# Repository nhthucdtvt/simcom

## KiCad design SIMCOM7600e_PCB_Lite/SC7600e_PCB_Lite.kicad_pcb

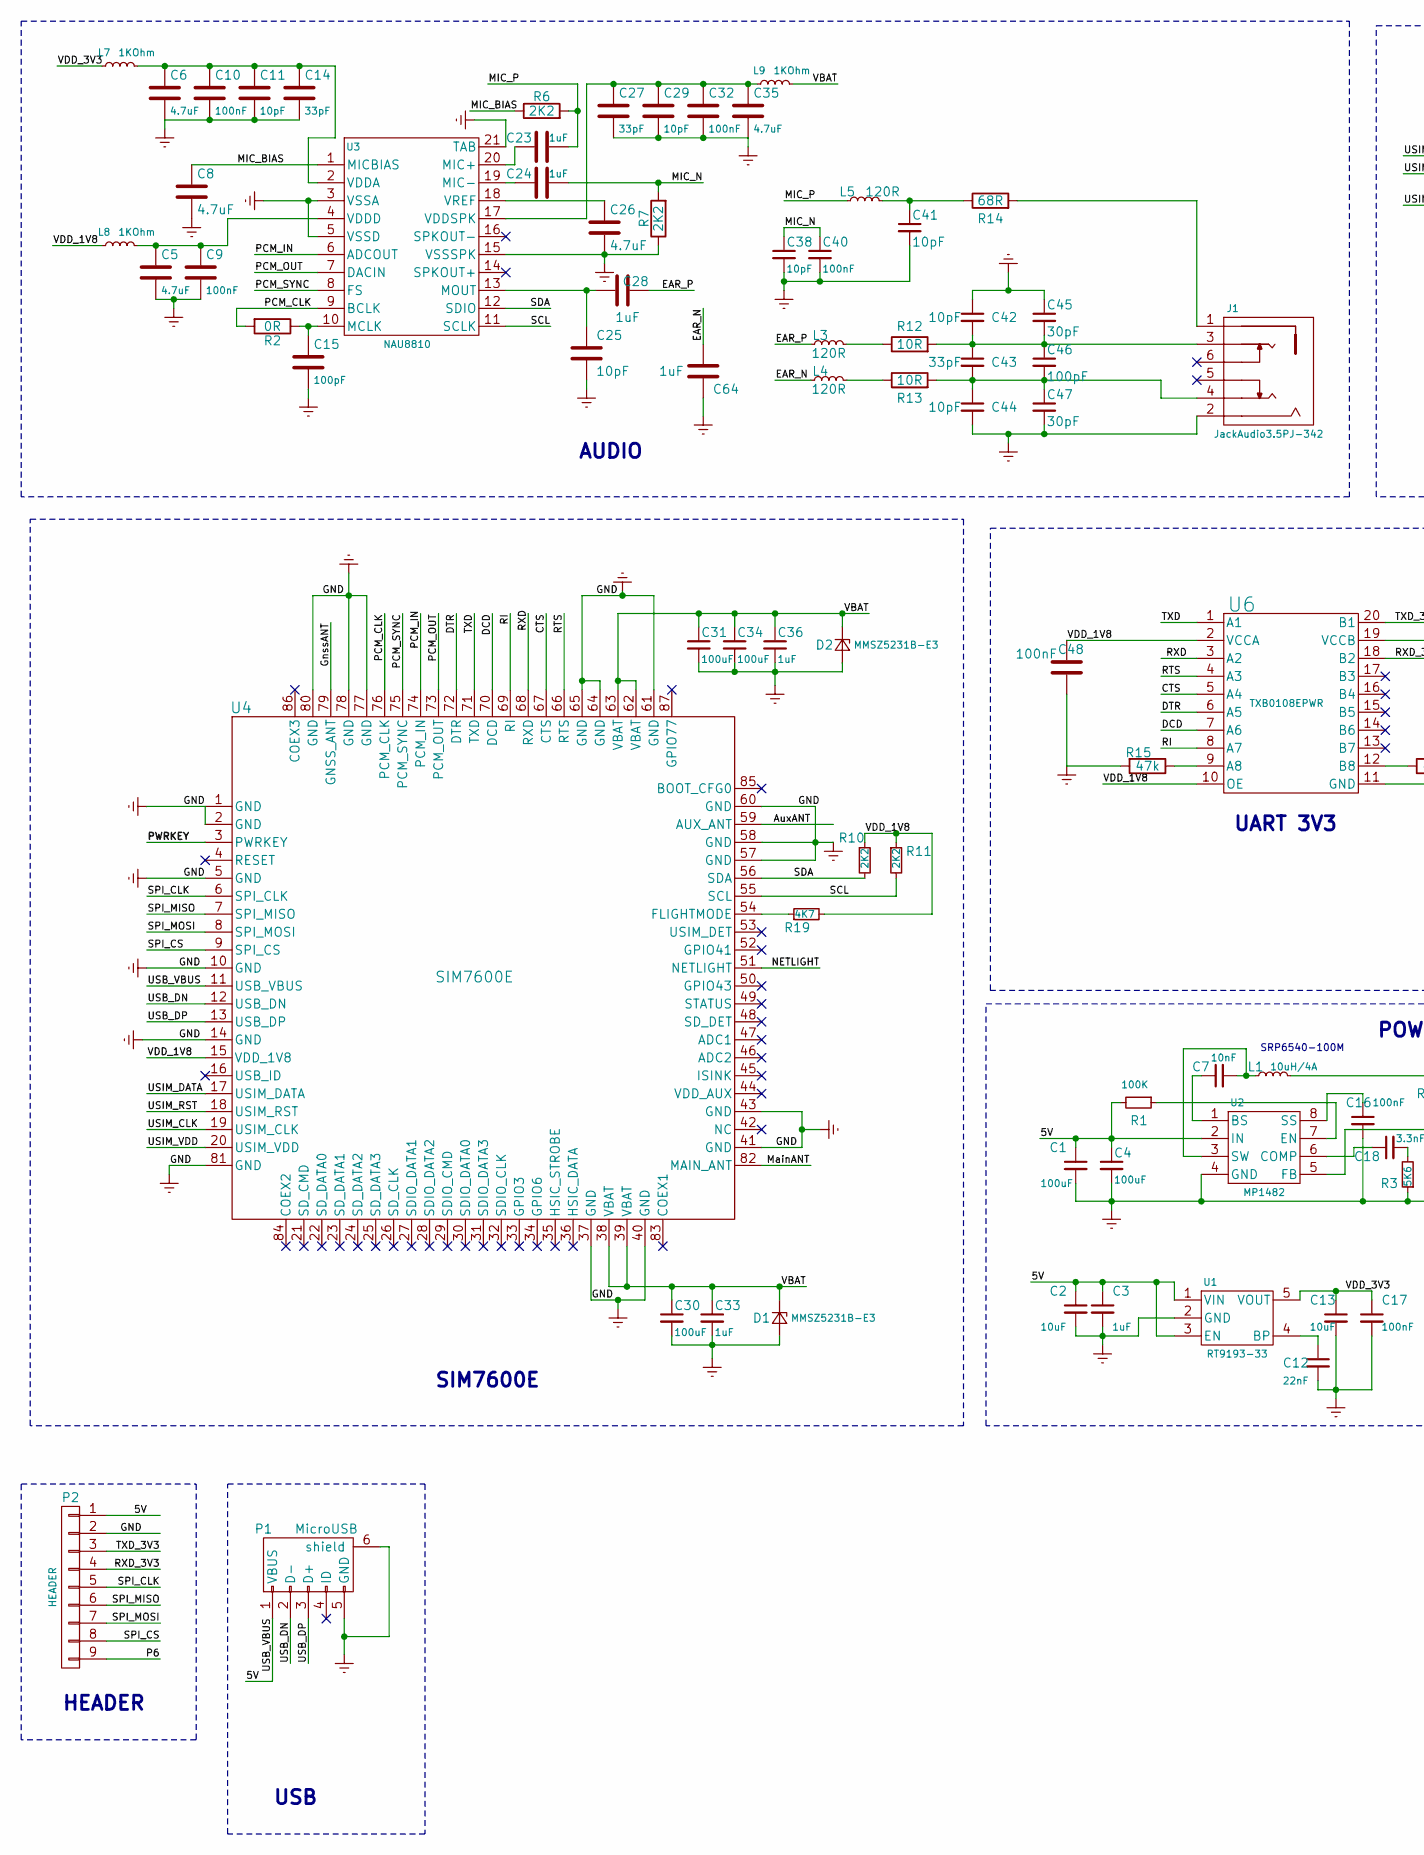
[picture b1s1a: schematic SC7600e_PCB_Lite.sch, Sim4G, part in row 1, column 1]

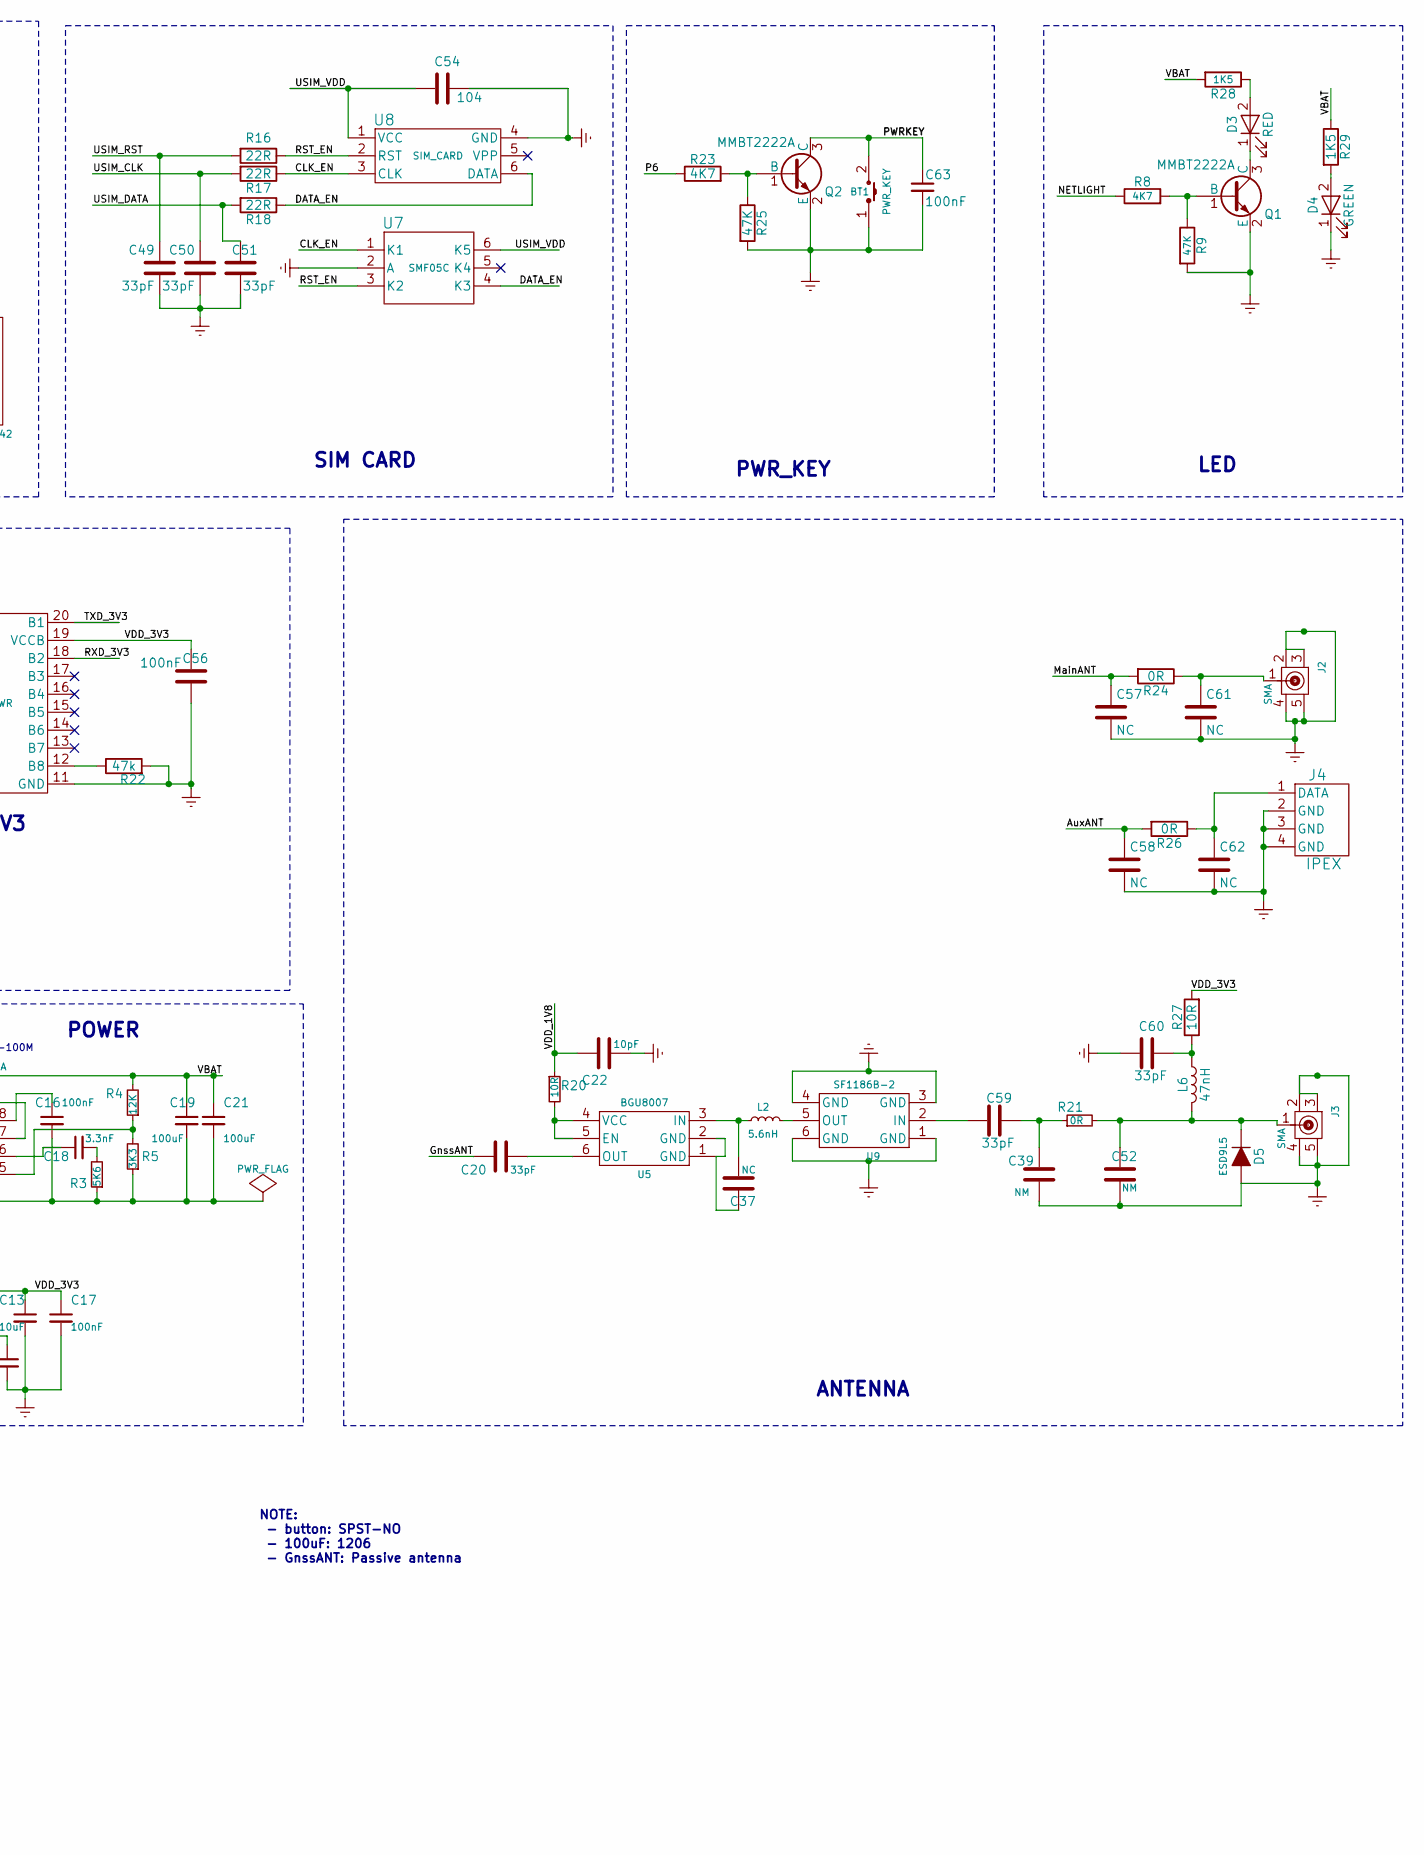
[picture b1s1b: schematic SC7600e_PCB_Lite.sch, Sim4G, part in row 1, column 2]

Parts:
BT1: PWR_KEY; SW_SPST_REED_CT05-XXXX-G1
C1, C19, C21, C30, C31, C34: 100uF; C_0805_2012Metric
C2, C13: 10uF; C_0603_1608Metric
C3, C23, C24, C28, C33, C36, C64: 1uF; C_0603_1608Metric
C4: 100uF; C_0603_1608Metric
C5, C6, C8, C26, C35: 4.7uF; C_0603_1608Metric
C7: 10nF; C_0603_1608Metric
C9, C10, C16, C17, C32, C40, C48, C56, C63: 100nF; C_0603_1608Metric
C11, C22, C25, C29, C38, C41, C42, C44: 10pF; C_0603_1608Metric
C12: 22nF; C_0603_1608Metric
C14, C27, C43, C49, C50, C51: 33pF; C_0603_1608Metric
C15, C46: 100pF; C_0603_1608Metric
C18: 3.3nF; C_0603_1608Metric
C20, C59, C60: 33pF; C_0402_1005Metric
C37, C57, C58, C61, C62: NC; C_0402_1005Metric
C39, C52: NM; C_0402_1005Metric
C45, C47: 30pF; C_0603_1608Metric
C54: 104; C_0603_1608Metric
D1, D2: MMSZ5231B-E3; D_SOD-123
D3: RED; LED_0603_1608Metric
D4: GREEN; LED_0603_1608Metric
D5: ESD9L5; SOD-923
J1: JackAudio3.5PJ-342; JackAudio3.5MM-PJ-342-6P
J2, J3: SMA; SMA_6x6x5.3_Vertical
J4: IPEX; IPEX_M_2.6x2.6x2
L1: 10uH/4A; L_7.2x6.5
L2: 5.6nH; L_0402_1005Metric
L3, L4, L5: 120R; R_0603_1608Metric
L6: 47nH; R_0402_1005Metric
L7: 1KOhm; R_0603_1608Metric
L8, L9: 1KOhm; L_0603_1608Metric
P1: MicroUSB; USB_Micro-B_Molex_47346-0001
P2: HEADER; Molex_KK-254_AE-6410-09A_1x09_P2.54mm_Vertical
Q1, Q2: MMBT2222A; SOT-23
R1: 100K; R_0603_1608Metric
R2: 0R; R_0603_1608Metric
R3: 5K6; R_0603_1608Metric
R4: 12K; R_0603_1608Metric
R5: 3K3; R_0603_1608Metric
R6, R7, R10, R11: 2K2; R_0603_1608Metric
R8, R19, R23: 4K7; R_0603_1608Metric
R9, R25: 47K; R_0603_1608Metric
R12, R13, R20, R27: 10R; R_0603_1608Metric
R14: 68R; R_0603_1608Metric
R15, R22: 47k; R_0603_1608Metric
R16, R17, R18: 22R; R_0603_1608Metric
R21, R24, R26: 0R; R_0402_1005Metric
R28, R29: 1K5; R_0603_1608Metric
U1: RT9193-33; SOT-23-5
U2: MP1482; SOIC-8_3.9x4.9mm_P1.27mm
U3: NAU8810; QFN-20-1EP_4x4mm_P0.5mm_EP2.5x2.5mm_ThermalVias
U4: SIM7600E
U5: BGU8007; SOT-886
U6: TXB0108EPWR; TSSOP-20_4.4x6.5mm_P0.65mm
U7: SMF05C; SC70-6
U8: SIM_CARD; CONN-GCT-SIM8050
U9: SF1186B-2; SF1186B2

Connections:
/5V: C1.1, C2.1, C3.1, C4.1, P1.1 (VBUS), P2.1, R1.2, U1.1 (VIN), U1.3 (EN), U2.2 (IN), U4.11 (USB_VBUS)
/AuxANT: C58.1, R26.2, U4.59 (AUX_ANT)
/CLK_EN: R17.1, U7.1 (K1), U8.3 (CLK)
/CTS: U4.67 (CTS), U6.5 (A4)
/DATA_EN: R18.1, U7.4 (K3), U8.6 (DATA)
/DCD: U4.70 (DCD), U6.7 (A6)
/DTR: U4.72 (DTR), U6.6 (A5)
/EAR_N: C64.1, L4.1
/EAR_P: C28.2, L3.1
/GnssANT: C20.1, U4.79 (GNSS_ANT)
/MIC_BIAS: C8.1, R6.1, U3.1 (MICBIAS)
/MIC_N: C24.2, C38.1, C40.1, R7.2
/MIC_P: C23.2, L5.1, R6.2
/MainANT: C57.1, R24.2, U4.82 (MAIN_ANT)
/NETLIGHT: R8.1, U4.51 (NETLIGHT)
/P6: P2.9, R23.1
/PCM_CLK: R2.2, U3.9 (BCLK), U4.76 (PCM_CLK)
/PCM_IN: U3.6 (ADCOUT), U4.74 (PCM_IN)
/PCM_OUT: U3.7 (DACIN), U4.73 (PCM_OUT)
/PCM_SYNC: U3.8 (FS), U4.75 (PCM_SYNC)
/PWRKEY: BT1.2, C63.1, Q2.3 (C), U4.3 (PWRKEY)
/RI: U4.69 (RI), U6.8 (A7)
/RST_EN: R16.1, U7.3 (K2), U8.2 (RST)
/RTS: U4.66 (RTS), U6.4 (A3)
/RXD: U4.68 (RXD), U6.3 (A2)
/RXD_3V3: P2.4, U6.18 (B2)
/SCL: R11.2, U3.11 (SCLK), U4.55 (SCL)
/SDA: R10.2, U3.12 (SDIO), U4.56 (SDA)
/SPI_CLK: P2.5, U4.6 (SPI_CLK)
/SPI_CS: P2.8, U4.9 (SPI_CS)
/SPI_MISO: P2.6, U4.7 (SPI_MISO)
/SPI_MOSI: P2.7, U4.8 (SPI_MOSI)
/TXD: U4.71 (TXD), U6.1 (A1)
/TXD_3V3: P2.3, U6.20 (B1)
/USB_DN: P1.2 (D-), U4.12 (USB_DN)
/USB_DP: P1.3 (D+), U4.13 (USB_DP)
/USIM_CLK: C50.2, R17.2, U4.19 (USIM_CLK)
/USIM_DATA: C51.2, R18.2, U4.17 (USIM_DATA)
/USIM_RST: C49.2, R16.2, U4.18 (USIM_RST)
/USIM_VDD: C54.2, U4.20 (USIM_VDD), U7.6 (K5), U8.1 (VCC)
/VBAT: C19.1, C21.1, C30.1, C31.1, C33.1, C34.1, C36.1, D1.1 (K), D2.1 (K), L1.2, L9.2, R4.2, R28.2, R29.1, U4.38 (VBAT), U4.39 (VBAT), U4.62 (VBAT), U4.63 (VBAT)
/VDD_1V8: C22.1, C48.2, L8.1, R10.1, R11.1, R19.2, R20.1, U4.15 (VDD_1V8), U6.2 (VCCA), U6.10 (OE)
/VDD_3V3: C13.1, C17.1, C56.2, L7.1, R27.2, U1.5 (VOUT), U6.19 (VCCB)
Earth: BT1.1, C1.2, C2.2, C3.2, C4.2, C5.2, C6.2, C8.2, C9.2, C10.2, C11.2, C12.2, C13.2, C14.2, C15.2, C16.2, C17.2, C19.2, C21.2, C22.2, C25.2, C26.2, C27.2, C29.2, C30.2, C31.2, C32.2, C33.2, C34.2, C35.2, C36.2, C38.2, C39.1, C40.2, C41.2, C42.1, C44.2, C45.1, C47.2, C48.1, C49.1, C50.1, C51.1, C52.1, C54.1, C56.1, C57.2, C58.2, C60.2, C61.2, C62.2, C63.2, C64.2, D1.2 (A), D2.2 (A), D4.1 (K), D5.2 (A), J1.2, J2.2, J2.3, J2.4, J2.5, J3.2, J3.3, J3.4, J3.5, J4.2 (GND), J4.3 (GND), J4.4 (GND), P1.5 (GND), P1.6 (shield), P2.2, Q1.2 (E), Q2.2 (E), R3.1, R5.1, R7.1, R9.2, R15.2, R22.2, R25.2, U1.2 (GND), U2.4 (GND), U3.3 (VSSA), U3.5 (VSSD), U3.15 (VSSSPK), U3.21 (TAB), U4.1 (GND), U4.2 (GND), U4.5 (GND), U4.10 (GND), U4.14 (GND), U4.37 (GND), U4.40 (GND), U4.41 (GND), U4.43 (GND), U4.57 (GND), U4.58 (GND), U4.60 (GND), U4.61 (GND), U4.64 (GND), U4.65 (GND), U4.77 (GND), U4.78 (GND), U4.80 (GND), U4.81 (GND), U6.11 (GND), U7.2 (A), U8.4 (GND), U9.1 (GND), U9.3 (GND), U9.4 (GND), U9.6 (GND)
unnamed: C5.1, C9.1, L8.2, U3.4 (VDDD)
unnamed: C7.1, U2.1 (BS)
unnamed: C7.2, L1.1, U2.3 (SW)
unnamed: C6.1, C10.1, C11.1, C14.1, L7.2, U3.2 (VDDA)
unnamed: C12.1, U1.4 (BP)
unnamed: C15.1, R2.1, U3.10 (MCLK)
unnamed: C16.1, U2.8 (SS)
unnamed: C18.1, U2.6 (COMP)
unnamed: C18.2, R3.2
unnamed: C20.2, U5.6 (OUT)
unnamed: C23.1, U3.20 (MIC+)
unnamed: C24.1, U3.19 (MIC-)
unnamed: C25.1, C28.1, U3.13 (MOUT)
unnamed: C26.1, U3.18 (VREF)
unnamed: C27.1, C29.1, C32.1, C35.1, L9.1, U3.17 (VDDSPK)
unnamed: C37.1, U5.1 (GND), U5.2 (GND)
unnamed: C37.2, L2.1, U5.3 (IN)
unnamed: C39.2, C59.1, R21.1
unnamed: C41.1, L5.2, R14.1
unnamed: C42.2, C43.1, C45.2, C46.1, J1.3, R12.2
unnamed: C43.2, C44.1, C46.2, C47.1, J1.4, R13.2
unnamed: C52.2, D5.1 (K), J3.1, L6.2, R21.2
unnamed: C59.2, U9.2 (IN)
unnamed: C60.1, L6.1, R27.1
unnamed: C61.1, J2.1, R24.1
unnamed: C62.1, J4.1 (DATA), R26.1
unnamed: D3.1 (K), Q1.3 (C)
unnamed: D3.2 (A), R28.1
unnamed: D4.2 (A), R29.2
unnamed: J1.1, R14.2
unnamed: L2.2, U9.5 (OUT)
unnamed: L3.2, R12.1
unnamed: L4.2, R13.1
unnamed: Q1.1 (B), R8.2, R9.1
unnamed: Q2.1 (B), R23.2, R25.1
unnamed: R1.1, U2.7 (EN)
unnamed: R4.1, R5.2, U2.5 (FB)
unnamed: R15.1, U6.9 (A8)
unnamed: R19.1, U4.54 (FLIGHTMODE)
unnamed: R20.2, U5.4 (VCC), U5.5 (EN)
unnamed: R22.1, U6.12 (B8)

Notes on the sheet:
ANTENNA
PWR_KEY
LED
SIM CARD
UART 3V3
USB
AUDIO
SIM7600E
POWER
HEADER
NOTE: - button: SPST-NO - 100uF: 1206 - GnssANT: Passive antenna
SRP6540-100M

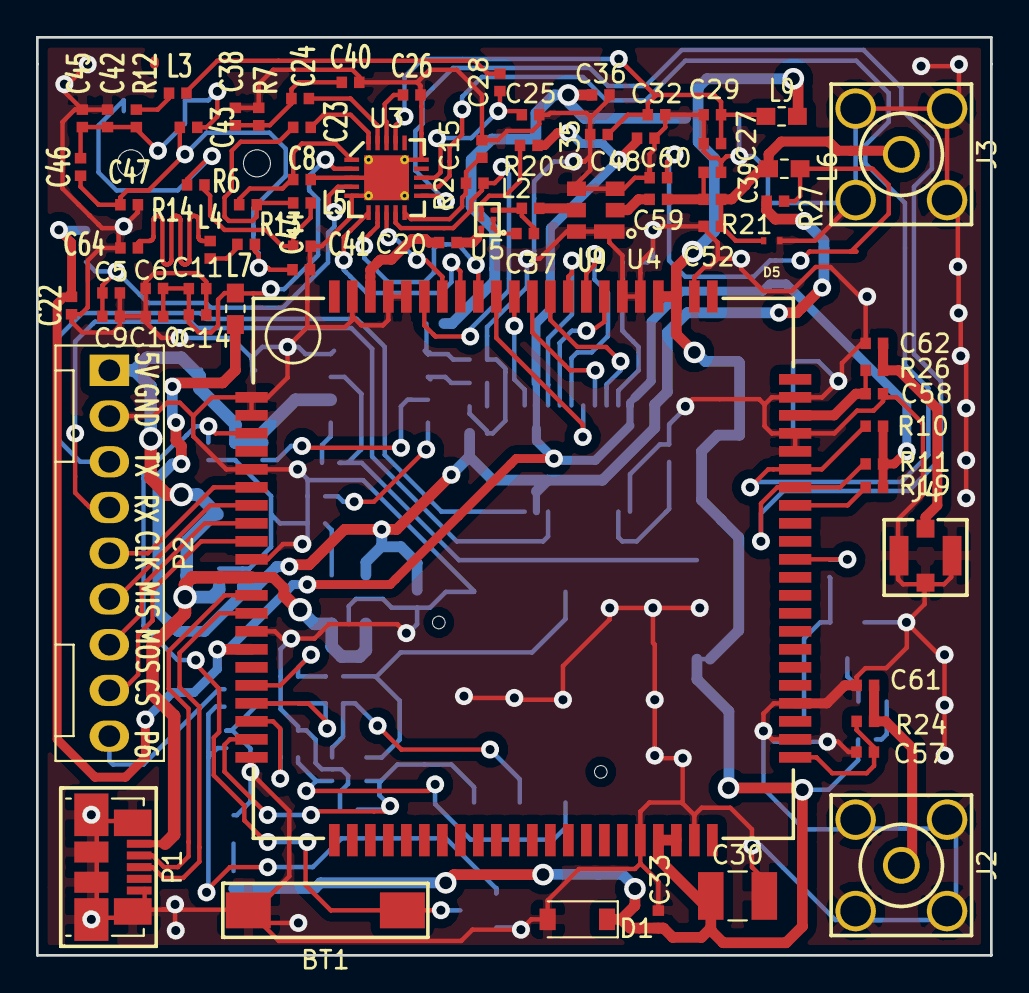
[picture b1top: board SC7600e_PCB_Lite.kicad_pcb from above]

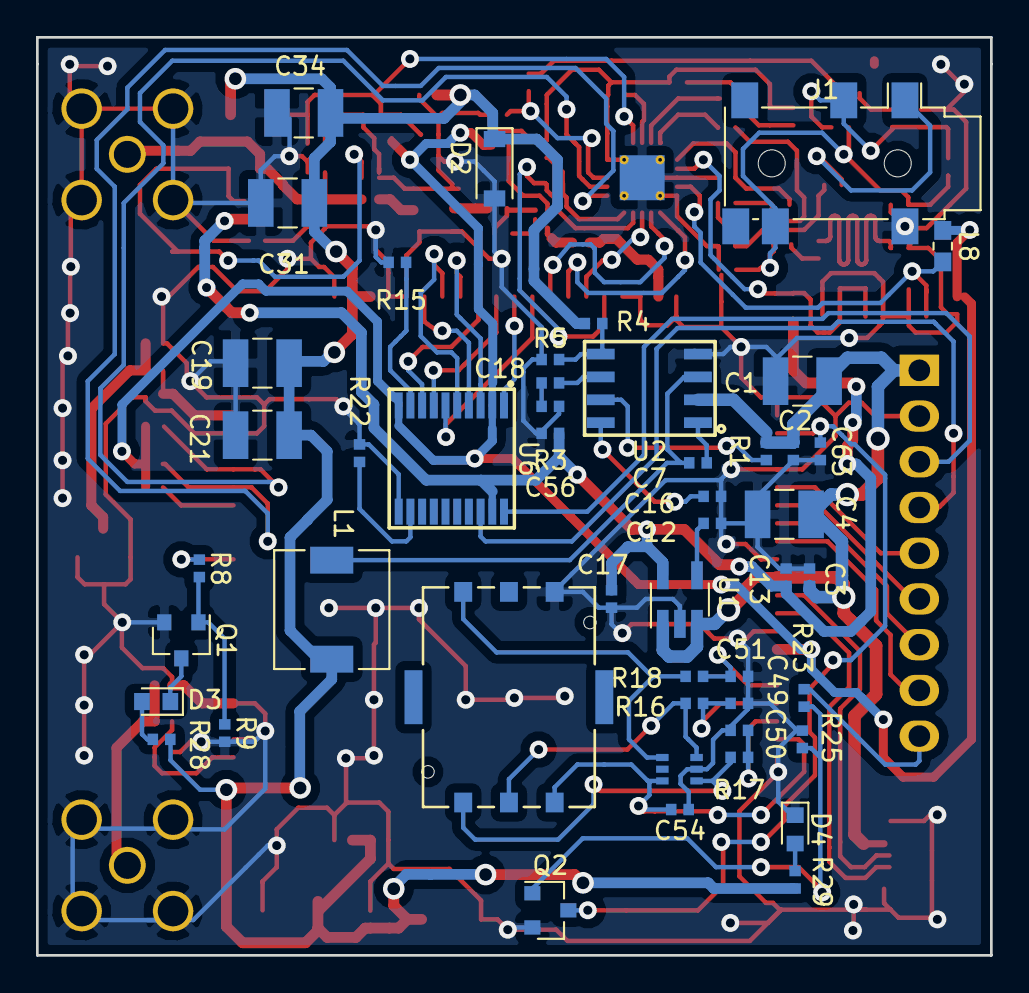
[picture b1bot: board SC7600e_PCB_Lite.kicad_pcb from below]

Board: 2 copper layers, 53.0 x 51.0 mm, 123 parts (48 on the bottom side), 85 nets.

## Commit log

2019-05-03 add files
